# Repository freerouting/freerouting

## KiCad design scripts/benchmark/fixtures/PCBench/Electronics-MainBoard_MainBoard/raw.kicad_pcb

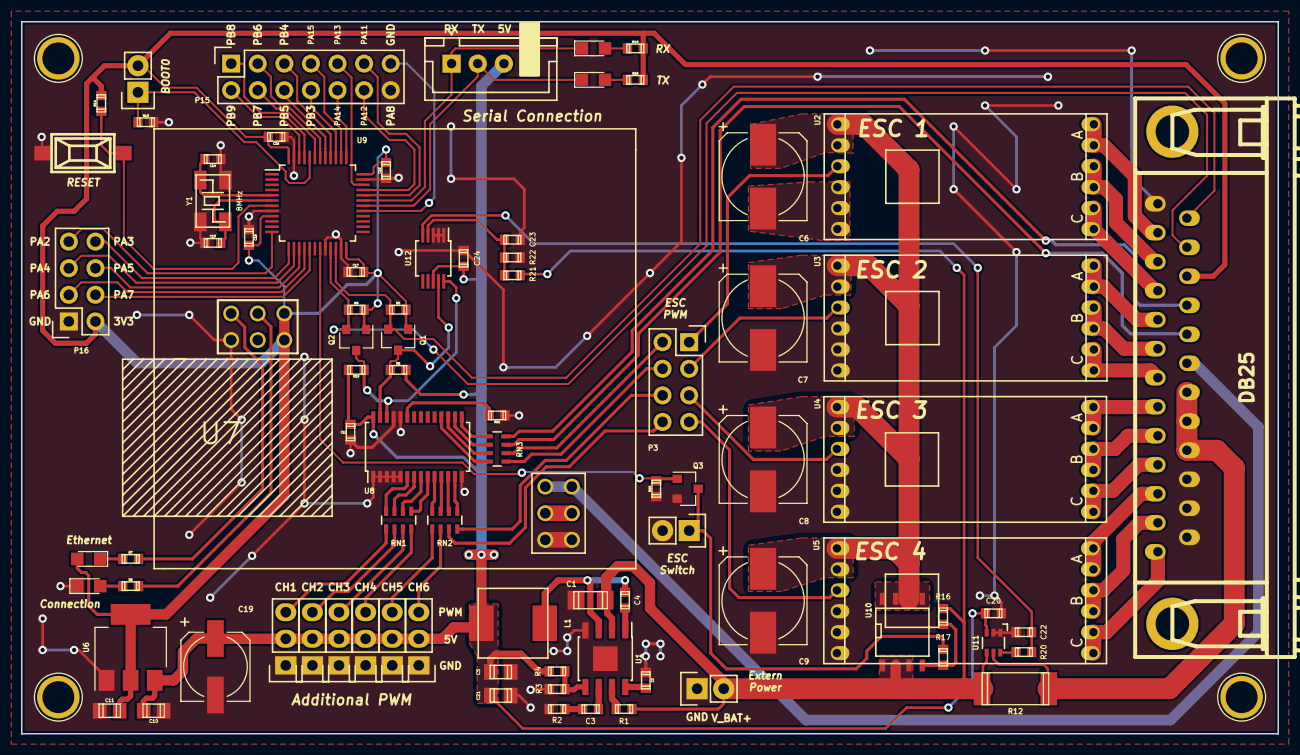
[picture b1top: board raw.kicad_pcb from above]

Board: 2 copper layers, 120.0 x 68.0 mm, 89 parts (0 on the bottom side), 96 nets.

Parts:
C1: 10uF/25V; c_1206
C2, C20, C23, C24: 0.1uF; c_0603
C3: 3.9nF; c_0603
C4: 10nF; c_0603
C5, C21: 22uF/10V; c_0805
C6, C7, C8, C9: 220uF/25V; CP_Elec_8x10
C10, C11: 1uF; c_0805
C12: 10uF; c_0603
C13, C14: 33pF; c_0603
C15, C16, C17, C18, C22: 1uF; c_0603
C19: 220uF/10V; CP_Elec_6.3x5.8
D1, D2, D3, D4: LED; LED_0805
J1: DB25; DB_25M
L1: 10uH/4A; ASPI-0630LR
P1: BOOT; Socket_Strip_Straight_1x02
P2: CONN_01X04; JST_XH_B04B-XH-A_04x2.50mm_Straight
P3, P16: CONN_02X04; Socket_Strip_Straight_2x04
P4, P5, P6, P7: HOLE; 1pin
P8, P14: CONN_01X02; Socket_Strip_Straight_1x02
P9, P10, P11, P12, P13, P18: CONN_01X03; Socket_Strip_Straight_1x03
P15: CONN_02X07; Socket_Strip_Straight_2x07
Q1, Q2: BSS138; SOT-23
Q3: DMN65D8L; SOT-23
R1: 100k; r_0603
R2: 6.8k; r_0603
R3: 10k 1%; r_0603
R4: 44.2k 1%; r_0603
R5, R8, R9, R10, R11, R13, R14, R15, R16: 10k; r_0603
R6, R7, R18, R19: 330; r_0603
R12: 0.003 %1; r_2512
R17: 1k; r_0603
R20: 3.3k; r_0603
R21: 30.1k %1; r_0603
R22: 10k %1; r_0603
RN1, RN2, RN3: 20k; R_Array_Concave_4x0603
SW1: RESET; smd_push
U1: mp2307; SOIC-8-1EP_3.9x4.9mm_Pitch1.27mm
U2, U3, U4, U5: DYS_mini_ESC; DYS_Mini_ESC
U6: TLV1117LV33; SOT-223
U7: TENDA_P200; Tenda_p200
U8: pca9685; TSSOP-28_4.4x9.7mm_Pitch0.65mm
U9: STM32F103CBT6; LQFP-48_7x7mm_Pitch0.5mm
U10: SI4425DDY; SOIC-8-N
U11: INA199A2; SC-70-6
U12: ADS1015; MSOP-10_3x3mm_Pitch0.5mm
Y1: 8MHz; crystal_maple

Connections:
/3V3: C11.1, C15.1, C16.1, C17.1, C18.1, D2.2, J1.23, P1.2, P16.2, Q1.1, Q2.1, R5.1, R9.1, R14.1, R18.1, R19.1, U6.2, U6.4, U7.3V3, U9.9, U9.24, U9.36, U9.48
/5V: C5.1, C10.1, C12.1, C19.1, C20.1, C21.1, C24.1, L1.2, P2.3, P9.2, P10.2, P11.2, P12.2, P13.2, P18.2, R4.1, R8.1, R10.1, U6.3, U8.28, U11.3, U12.8
/ADC_I: C22.1, R20.1, U12.5
/ADC_V: C23.1, R21.2, R22.1, U12.4
/CH0: P9.3, RN1.1
/CH1: P10.3, RN1.2
/CH2: P11.3, RN1.3
/CH3: P12.3, RN1.4
/CH4: P13.3, RN2.1
/CH5: P18.3, RN2.2
/CH6: P3.8, RN2.3
/CH7: P3.6, RN2.4
/CH10: P3.2, RN3.6
/CH11: P3.4, RN3.5
/ESC1: P3.1, U2.2
/ESC2: P3.3, U3.2
/ESC3: P3.5, U4.2
/ESC4: P3.7, U5.2
/LED1: J1.21, RN3.7
/LED2: J1.22, RN3.8
/MOTOR_1A: J1.12, U2.4
/MOTOR_1B: J1.11, U2.5
/MOTOR_1C: J1.10, U2.6
/MOTOR_2A: J1.9, U3.4
/MOTOR_2B: J1.8, U3.5
/MOTOR_2C: J1.7, U3.6
/MOTOR_3A: J1.6, U4.4
/MOTOR_3B: J1.5, U4.5
/MOTOR_3C: J1.4, U4.6
/MOTOR_4A: J1.3, U5.4
/MOTOR_4B: J1.2, U5.5
/MOTOR_4C: J1.1, U5.6
/OSC_N: C14.1, U9.5, Y1.2
/OSC_P: C13.1, U9.6, Y1.1
/PA2: P16.7, U9.12
/PA3: P16.8, U9.13
/PA4: P16.5, U9.14
/PA5: P16.6, U9.15
/PA6: P16.3, U9.16
/PA7: P16.4, U9.17
/PA8: P15.13, U9.29
/PA11: P15.11, U9.32
/PA12: P15.12, U9.33
/PA13: P15.9, U9.34
/PA14: P15.10, U9.37
/PA15: P15.7, U9.38
/PB3: P15.8, U9.39
/PB4: P15.5, U9.40
/PB5: P15.6, U9.41
/PB6: P15.3, U9.42
/PB7: P15.4, U9.43
/PB8: P15.1, U9.45
/PB9: P15.2, U9.46
/PWR_SW: Q3.1, R15.1, U9.19
/RX1: D4.1, P2.1, U9.31
/SCL_3V3: J1.24, Q2.2, R9.2, U9.21
/SCL_5V: Q2.3, R10.2, U8.26, U12.10
/SDA_3V3: J1.25, Q1.2, R5.2, U9.22
/SDA_5V: Q1.3, R8.2, U8.27, U12.9
/T+: J1.20, U7.T_+
/TX1: D3.1, P2.2, U9.30
/V_BAT: C1.1, P8.2, R1.1, R12.1, R16.1, R21.1, U1.2, U10.1, U10.2, U10.3, U11.4
/V_IN: J1.17, J1.18, J1.19, R12.2, U11.5
/V_PWR: C6.1, C7.1, C8.1, C9.1, U2.3, U3.3, U4.3, U5.3, U10.5, U10.6, U10.7, U10.8
GND: C1.2, C2.2, C5.2, C6.2, C7.2, C8.2, C9.2, C10.2, C11.2, C12.2, C13.2, C14.2, C15.2, C16.2, C17.2, C18.2, C19.2, C20.2, C21.2, C22.2, C23.2, C24.2, D1.1, J1.13, J1.14, J1.15, J1.16, P2.4, P8.1, P9.1, P10.1, P11.1, P12.1, P13.1, P14.2, P15.14, P16.1, P18.1, Q3.2, R2.2, R3.2, R11.2, R13.1, R15.2, R22.2, SW1.1, U1.4, U1.9, U2.1, U3.1, U4.1, U5.1, U6.1, U7.GND, U7.T_-, U8.1, U8.2, U8.3, U8.4, U8.5, U8.14, U8.24, U8.25, U9.8, U9.20, U9.23, U9.35, U9.47, U11.1, U11.2, U12.1, U12.2, U12.3, Y1.3
unnamed: C2.1, U1.8
unnamed: C3.1, U1.6
unnamed: C3.2, R2.1
unnamed: C4.1, L1.1, U1.3
unnamed: C4.2, U1.1
unnamed: D1.2, R6.2
unnamed: D2.1, R7.2
unnamed: D3.2, R18.2
unnamed: D4.2, R19.2
unnamed: P1.1, R13.2, U9.44
unnamed: P14.1, Q3.3, R17.2
unnamed: R1.2, U1.7
unnamed: R3.1, R4.2, U1.5
unnamed: R6.1, U7.C
unnamed: R7.1, U7.E
unnamed: R11.1, U8.23
unnamed: R14.2, SW1.2, U9.7
unnamed: R16.2, R17.1, U10.4
unnamed: R20.2, U11.6
unnamed: RN1.5, U8.9
unnamed: RN1.6, U8.8
unnamed: RN1.7, U8.7
unnamed: RN1.8, U8.6
unnamed: RN2.5, U8.13
unnamed: RN2.6, U8.12
unnamed: RN2.7, U8.11
unnamed: RN2.8, U8.10
unnamed: RN3.1, U8.15
unnamed: RN3.2, U8.16
unnamed: RN3.3, U8.17
unnamed: RN3.4, U8.18

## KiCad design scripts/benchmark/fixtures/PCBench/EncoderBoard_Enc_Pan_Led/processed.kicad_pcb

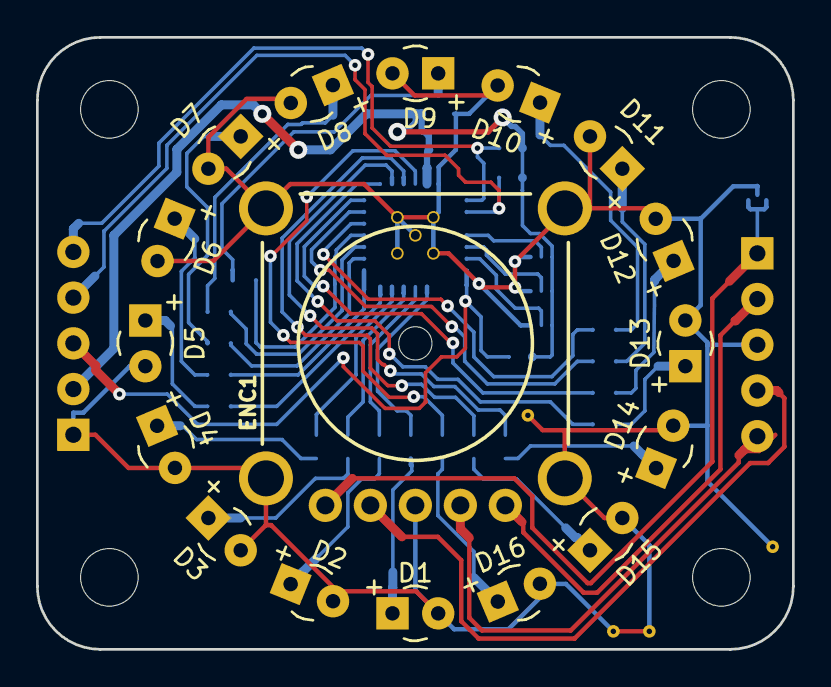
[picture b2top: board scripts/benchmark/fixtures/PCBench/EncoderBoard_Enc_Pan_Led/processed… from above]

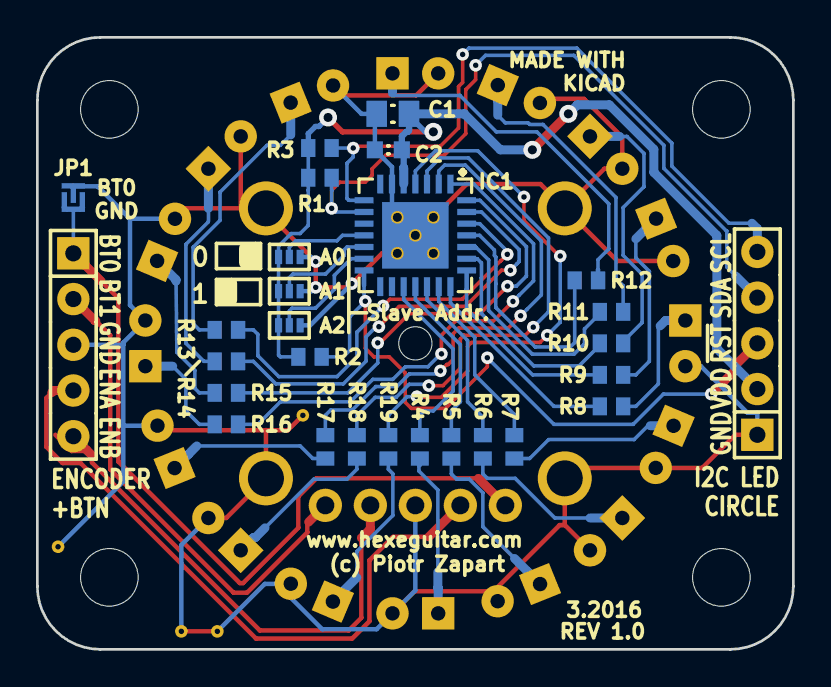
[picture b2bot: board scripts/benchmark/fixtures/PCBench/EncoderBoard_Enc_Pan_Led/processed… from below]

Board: 2 copper layers, 42.0 x 34.0 mm, 58 parts (28 on the bottom side), 44 nets.

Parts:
C1: 10µ; CAPC_0805_2012X70N
C2: 100n; CAPC_0603_1608X55N
D1, D2, D3, D4, D5, D6, D7, D8, D9, D10, D11, D12, D13, D14, D15, D16: LED; Diode_LED_3mm_round_vertical
ENC1: Panasonic_EVEP_encoder; PanasonicEVEP_Encoder
IC1: MCP23017_QFN; QFN65P600X600X100-29VN
JP1: Jumper_NO_Small; PCB_jumper_2
MP1, MP2, MP3, MP4: SCREW; MountingHole_3-5mm
P1, P2: CONN_01X05; 1x5_254
R1, R3: 2k2; RESC_0603_1508X63N
R2: 10k; RESC_0603_1508X63N
R4, R5, R6, R7, R8, R9, R10, R11, R12, R13, R14, R15, R16, R17, R18, R19: R; RESC_0603_1508X63N
SW1, SW2, SW3: PCB_SPDT; SPDT_BlobSwitch_SMD
Via0703_GND, Via0703_GND_2, Via0703_GND_3, Via0703_GND_4, Via0703_GND_5, Via0703_GND_6, Via0703_GND_7, Via0703_GND_8, Via0703_GND_9: VAL**; Via0703_GND

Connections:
/BTN0: ENC1.1, JP1.1, P1.1
/BTN1: ENC1.5, P1.2
/ENC_A: ENC1.2, P1.4
/ENC_B: ENC1.4, P1.5
/LED0: IC1.17, R4.2
/LED1: IC1.18, R5.2
/LED2: IC1.19, R6.2
/LED3: IC1.20, R7.2
/LED4: IC1.21, R8.2
/LED5: IC1.22, R9.2
/LED6: IC1.23, R10.2
/LED7: IC1.24, R11.2
/LED8: IC1.25, R12.2
/LED9: IC1.26, R13.2
/LED10: IC1.27, R14.2
/LED11: IC1.28, R15.2
/LED12: IC1.1, R16.2
/LED13: IC1.2, R17.2
/LED14: IC1.3, R18.2
/LED15: IC1.4, R19.2
/SCL: IC1.8, P2.5, R3.1
/SDA: IC1.9, P2.4, R1.1
/VDD: C1.1, C2.1, IC1.5, P2.2, R1.2, R2.2, R3.2, SW1.3, SW2.3, SW3.3
/~RESET: IC1.14, P2.3, R2.1
GND: C1.2, C2.2, D1.2, D2.2, D3.2, D4.2, D5.2, D6.2, D7.2, D8.2, D9.2, D10.2, D11.2, D12.2, D13.2, D14.2, D15.2, D16.2, ENC1.3, ENC1.6, ENC1.7, ENC1.8, ENC1.9, IC1.6, IC1.29, JP1.2, P1.3, P2.1, SW1.1, SW2.1, SW3.1, Via0703_GND.1, Via0703_GND_2.1, Via0703_GND_3.1, Via0703_GND_4.1, Via0703_GND_5.1, Via0703_GND_6.1, Via0703_GND_7.1, Via0703_GND_8.1, Via0703_GND_9.1
unnamed: D1.1, R4.1
unnamed: D2.1, R5.1
unnamed: D3.1, R6.1
unnamed: D4.1, R7.1
unnamed: D5.1, R8.1
unnamed: D6.1, R9.1
unnamed: D7.1, R10.1
unnamed: D8.1, R11.1
unnamed: D9.1, R12.1
unnamed: D10.1, R13.1
unnamed: D11.1, R14.1
unnamed: D12.1, R15.1
unnamed: D13.1, R16.1
unnamed: D14.1, R17.1
unnamed: D15.1, R18.1
unnamed: D16.1, R19.1
unnamed: IC1.11, SW1.2
unnamed: IC1.12, SW2.2
unnamed: IC1.13, SW3.2

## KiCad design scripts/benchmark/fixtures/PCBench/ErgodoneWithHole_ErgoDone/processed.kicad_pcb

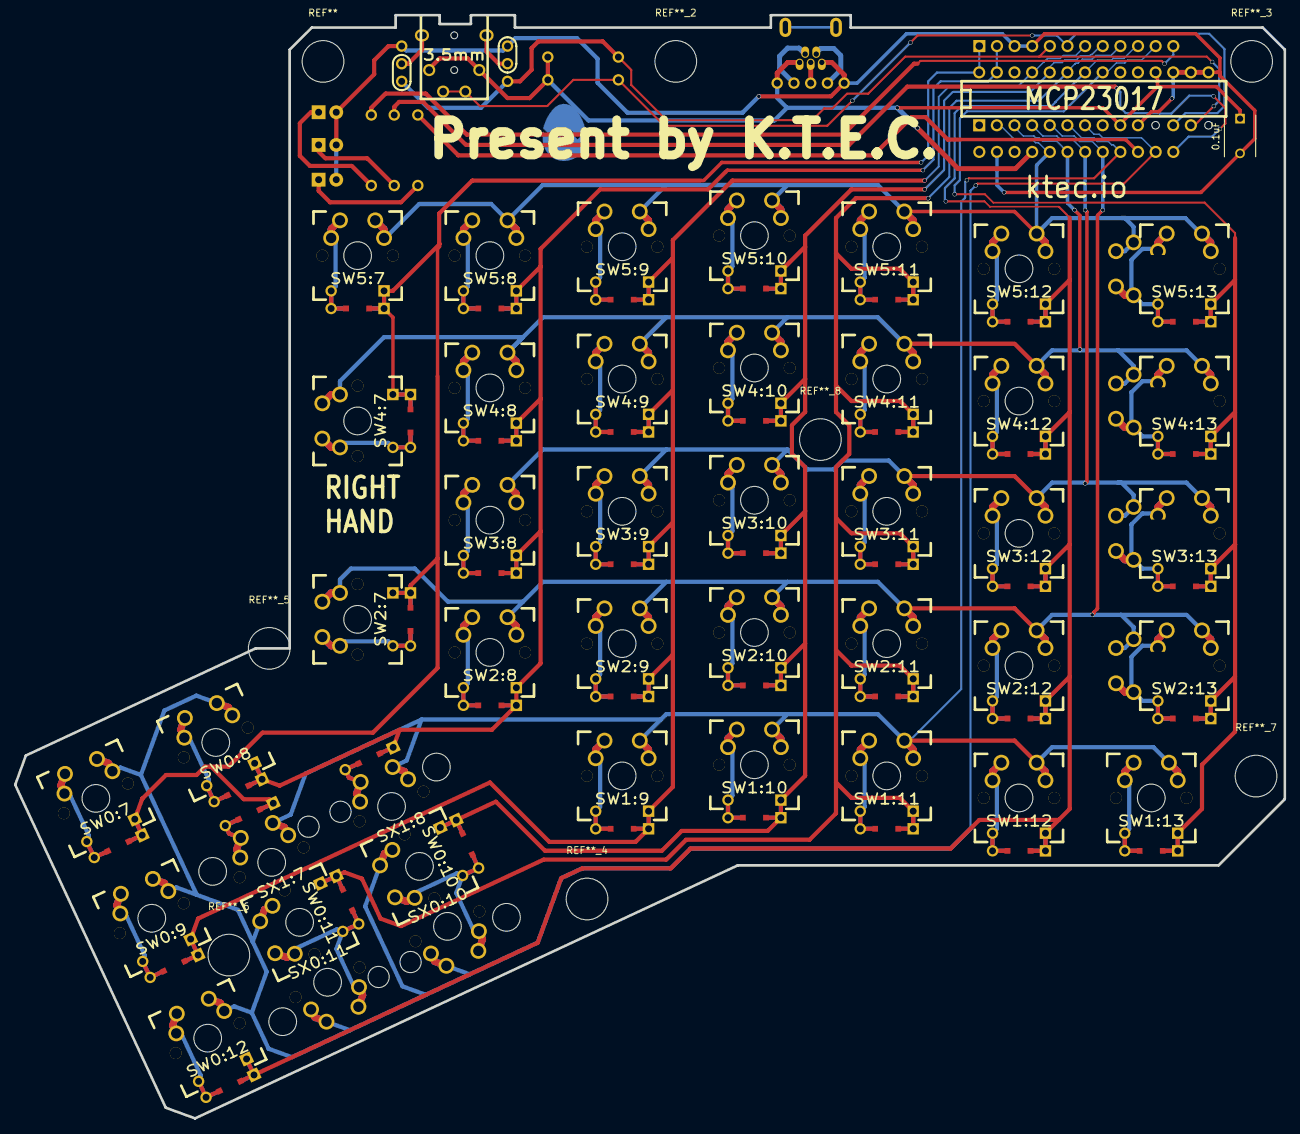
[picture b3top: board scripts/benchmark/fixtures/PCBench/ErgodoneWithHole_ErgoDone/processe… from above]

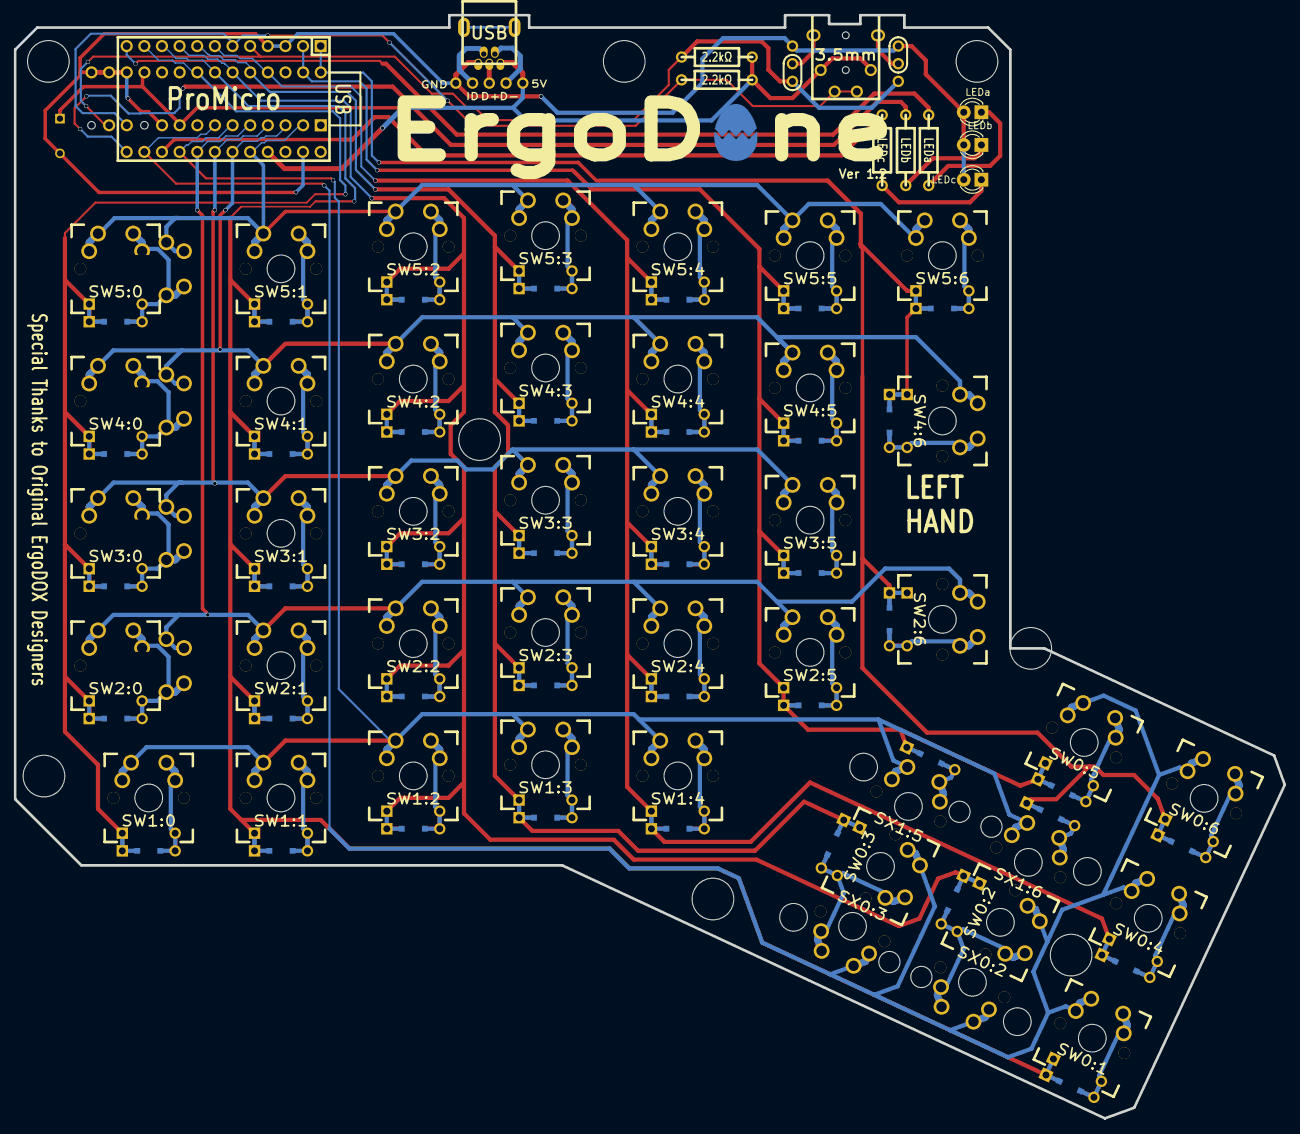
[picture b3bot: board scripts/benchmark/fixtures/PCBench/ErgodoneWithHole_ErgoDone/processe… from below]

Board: 2 copper layers, 182.8 x 158.9 mm, 61 parts (11 on the bottom side), 65 nets.

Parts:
C1: 0.1uF; C_Disc_D6_P5
D1:7, D1:8: D; DIODE
J1: USB; USBMINImod
J2: 3.5mm; 4pin35mmAudio
J3, J4: JMP; 100PITCH1X3
LEDa: LEDa; LED-3MM
LEDb: LEDb; LED-3MM
LEDc: LEDc; LED-3MM
R1, R2: 2.2kΩ; RESISTOR
RA1: LEDa; RESISTOR
RB1: LEDb; RESISTOR
RC1: LEDc; RESISTOR
S1, S2: STAB200; STAB_PCB940
SW0:7: SW0:6; MX_FLIP_DIODE
SW0:8: SW0:5; MX_FLIP_DIODE
SW0:9: SW0:4; MX_FLIP_DIODE
SW0:10: SW0:3; MX_FLIP_DIODE
SW0:11: SW0:2; MX_FLIP_DIODE
SW0:12: SW0:1; MX_FLIP_DIODE
SW1:9: SW1:4; MX_FLIP_DIODE
SW1:10: SW1:3; MX_FLIP_DIODE
SW1:11: SW1:2; MX_FLIP_DIODE
SW1:12: SW1:1; MX_FLIP_DIODE
SW1:13: SW1:0; MX_FLIP_DIODE
SW2:7: SW2:6; MX_FLIP_DIODE
SW2:8: SW2:5; MX_FLIP_DIODE
SW2:9: SW2:4; MX_FLIP_DIODE
SW2:10: SW2:3; MX_FLIP_DIODE
SW2:11: SW2:2; MX_FLIP_DIODE
SW2:12: SW2:1; MX_FLIP_DIODE
SW2:13: SW2:0; MX_FLIP_XX
SW3:8: SW3:5; MX_FLIP_DIODE
SW3:9: SW3:4; MX_FLIP_DIODE
SW3:10: SW3:3; MX_FLIP_DIODE
SW3:11: SW3:2; MX_FLIP_DIODE
SW3:12: SW3:1; MX_FLIP_DIODE
SW3:13: SW3:0; MX_FLIP_XX
SW4:7: SW4:6; MX_FLIP_DIODE
SW4:8: SW4:5; MX_FLIP_DIODE
SW4:9: SW4:4; MX_FLIP_DIODE
SW4:10: SW4:3; MX_FLIP_DIODE
SW4:11: SW4:2; MX_FLIP_DIODE
SW4:12: SW4:1; MX_FLIP_DIODE
SW4:13: SW4:0; MX_FLIP_XX
SW5:7: SW5:6; MX_FLIP_DIODE
SW5:8: SW5:5; MX_FLIP_DIODE
SW5:9: SW5:4; MX_FLIP_DIODE
SW5:10: SW5:3; MX_FLIP_DIODE
SW5:11: SW5:2; MX_FLIP_DIODE
SW5:12: SW5:1; MX_FLIP_DIODE
SW5:13: SW5:0; MX_FLIP_XX
SX0:10: SX0:3; MX_FLIP
SX0:11: SX0:2; MX_FLIP
SX1:7: SX1:6; MX_FLIP
SX1:8: SX1:5; MX_FLIP
U1: ProMicro; TEENSY_2.0
U2: MCP23017

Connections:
/COL0: SW1:13.4, SW2:13.4, SW3:13.4, SW4:13.4, SW5:13.4, U1.11, U2.21
/COL1: SW0:12.4, SW1:12.4, SW2:12.4, SW3:12.4, SW4:12.4, SW5:12.4, U1.10, U2.22
/COL4: SW0:9.4, SW1:9.4, SW2:9.4, SW3:9.4, SW4:9.4, SW5:9.4, U1.7, U2.25
/COL5: D1:8.2, SW0:8.4, SW2:8.4, SW3:8.4, SW4:8.4, SW5:8.4, U1.2, U2.27
/COL6: D1:7.2, SW0:7.4, SW2:7.4, SW4:7.4, SW5:7.4, U1.1, U2.28
/COL10: SW0:10.4, SW1:10.4, SW2:10.4, SW3:10.4, SW4:10.4, SW5:10.4, U1.8, U2.24
/COL11: SW0:11.4, SW1:11.4, SW2:11.4, SW3:11.4, SW4:11.4, SW5:11.4, U1.9, U2.23
/LED_A: RA1.1, U1.12
/LED_B: RB1.1, U1.18
/LED_C: RC1.1, U1.20
/ROW0: SW0:7.1, SW0:8.1, SW0:9.1, SW0:10.1, SW0:11.1, SW0:12.1, SX0:10.1, SX0:11.1, U1.19, U2.7
/ROW1: SW1:9.1, SW1:10.1, SW1:11.1, SW1:12.1, SW1:13.1, SX1:7.1, SX1:8.1, U1.21, U2.6
/ROW2: SW2:7.1, SW2:8.1, SW2:9.1, SW2:10.1, SW2:11.1, SW2:12.1, SW2:13.1, U1.22, U2.5
/ROW3: SW3:8.1, SW3:9.1, SW3:10.1, SW3:11.1, SW3:12.1, SW3:13.1, U1.23, U2.4
/ROW4: SW4:7.1, SW4:8.1, SW4:9.1, SW4:10.1, SW4:11.1, SW4:12.1, SW4:13.1, U1.24, U2.3
/ROW5: SW5:7.1, SW5:8.1, SW5:9.1, SW5:10.1, SW5:11.1, SW5:12.1, SW5:13.1, U1.25, U2.2
/SCLM: J2.3, J2.5, R2.2, U1.6, U2.12
/SDAM: J3.1, J4.1, R1.2, U1.5, U2.13
GND: C1.2, J1.5, J3.3, J4.3, LEDa.2, LEDb.2, LEDc.2, U1.3, U1.4, U1.28, U2.10, U2.15, U2.16, U2.17
unnamed: D1:7.1, SX1:7.2
unnamed: D1:8.1, SX1:8.2
unnamed: J2.1, J3.2
unnamed: J2.4, J4.2
unnamed: LEDa.1, RA1.2
unnamed: LEDb.1, RB1.2
unnamed: LEDc.1, RC1.2
unnamed: SW0:7.2, SW0:7.3
unnamed: SW0:8.2, SW0:8.3
unnamed: SW0:9.2, SW0:9.3
unnamed: SW0:10.2, SW0:10.3, SX0:10.2
unnamed: SW0:11.2, SW0:11.3, SX0:11.2
unnamed: SW0:12.2, SW0:12.3
unnamed: SW1:9.2, SW1:9.3
unnamed: SW1:10.2, SW1:10.3
unnamed: SW1:11.2, SW1:11.3
unnamed: SW1:12.2, SW1:12.3
unnamed: SW1:13.2, SW1:13.3
unnamed: SW2:7.2, SW2:7.3
unnamed: SW2:8.2, SW2:8.3
unnamed: SW2:9.2, SW2:9.3
unnamed: SW2:10.2, SW2:10.3
unnamed: SW2:11.2, SW2:11.3
unnamed: SW2:12.2, SW2:12.3
unnamed: SW2:13.2, SW2:13.3
unnamed: SW3:8.2, SW3:8.3
unnamed: SW3:9.2, SW3:9.3
unnamed: SW3:10.2, SW3:10.3
unnamed: SW3:11.2, SW3:11.3
unnamed: SW3:12.2, SW3:12.3
unnamed: SW3:13.2, SW3:13.3
unnamed: SW4:7.2, SW4:7.3
unnamed: SW4:8.2, SW4:8.3
unnamed: SW4:9.2, SW4:9.3
unnamed: SW4:10.2, SW4:10.3
unnamed: SW4:11.2, SW4:11.3
unnamed: SW4:12.2, SW4:12.3
unnamed: SW4:13.2, SW4:13.3
unnamed: SW5:7.2, SW5:7.3
unnamed: SW5:8.2, SW5:8.3
unnamed: SW5:9.2, SW5:9.3
unnamed: SW5:10.2, SW5:10.3
unnamed: SW5:11.2, SW5:11.3
unnamed: SW5:12.2, SW5:12.3
unnamed: SW5:13.2, SW5:13.3
VCC: C1.1, J1.1, J2.2, J2.6, R1.1, R2.1, U1.26, U2.9, U2.18
